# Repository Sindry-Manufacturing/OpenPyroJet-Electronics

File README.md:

# OpenPyroJet-Electronics

Software licensed under: AGPL-3

Hardware licensed under: CERN-OHL-S-V2

These sets of sub-folders contain KiCAD 5.1 based designs for experimenting with a PCB based metal/ceramic 3D Printer. 

Gen3.1_Printhead       ; initial experimental PCB based Printhead

Printhead-Controller   ; HW board that runs the Driver board

Printhead-Driver       ; HW circuitry to drive the printhead

software               ; basic Arduino based software to test the Controller & Driver boards.  See: https://github.com/Sindry-Manufacturing/OpenPyrojet-Jetpack  for a much more complete solution

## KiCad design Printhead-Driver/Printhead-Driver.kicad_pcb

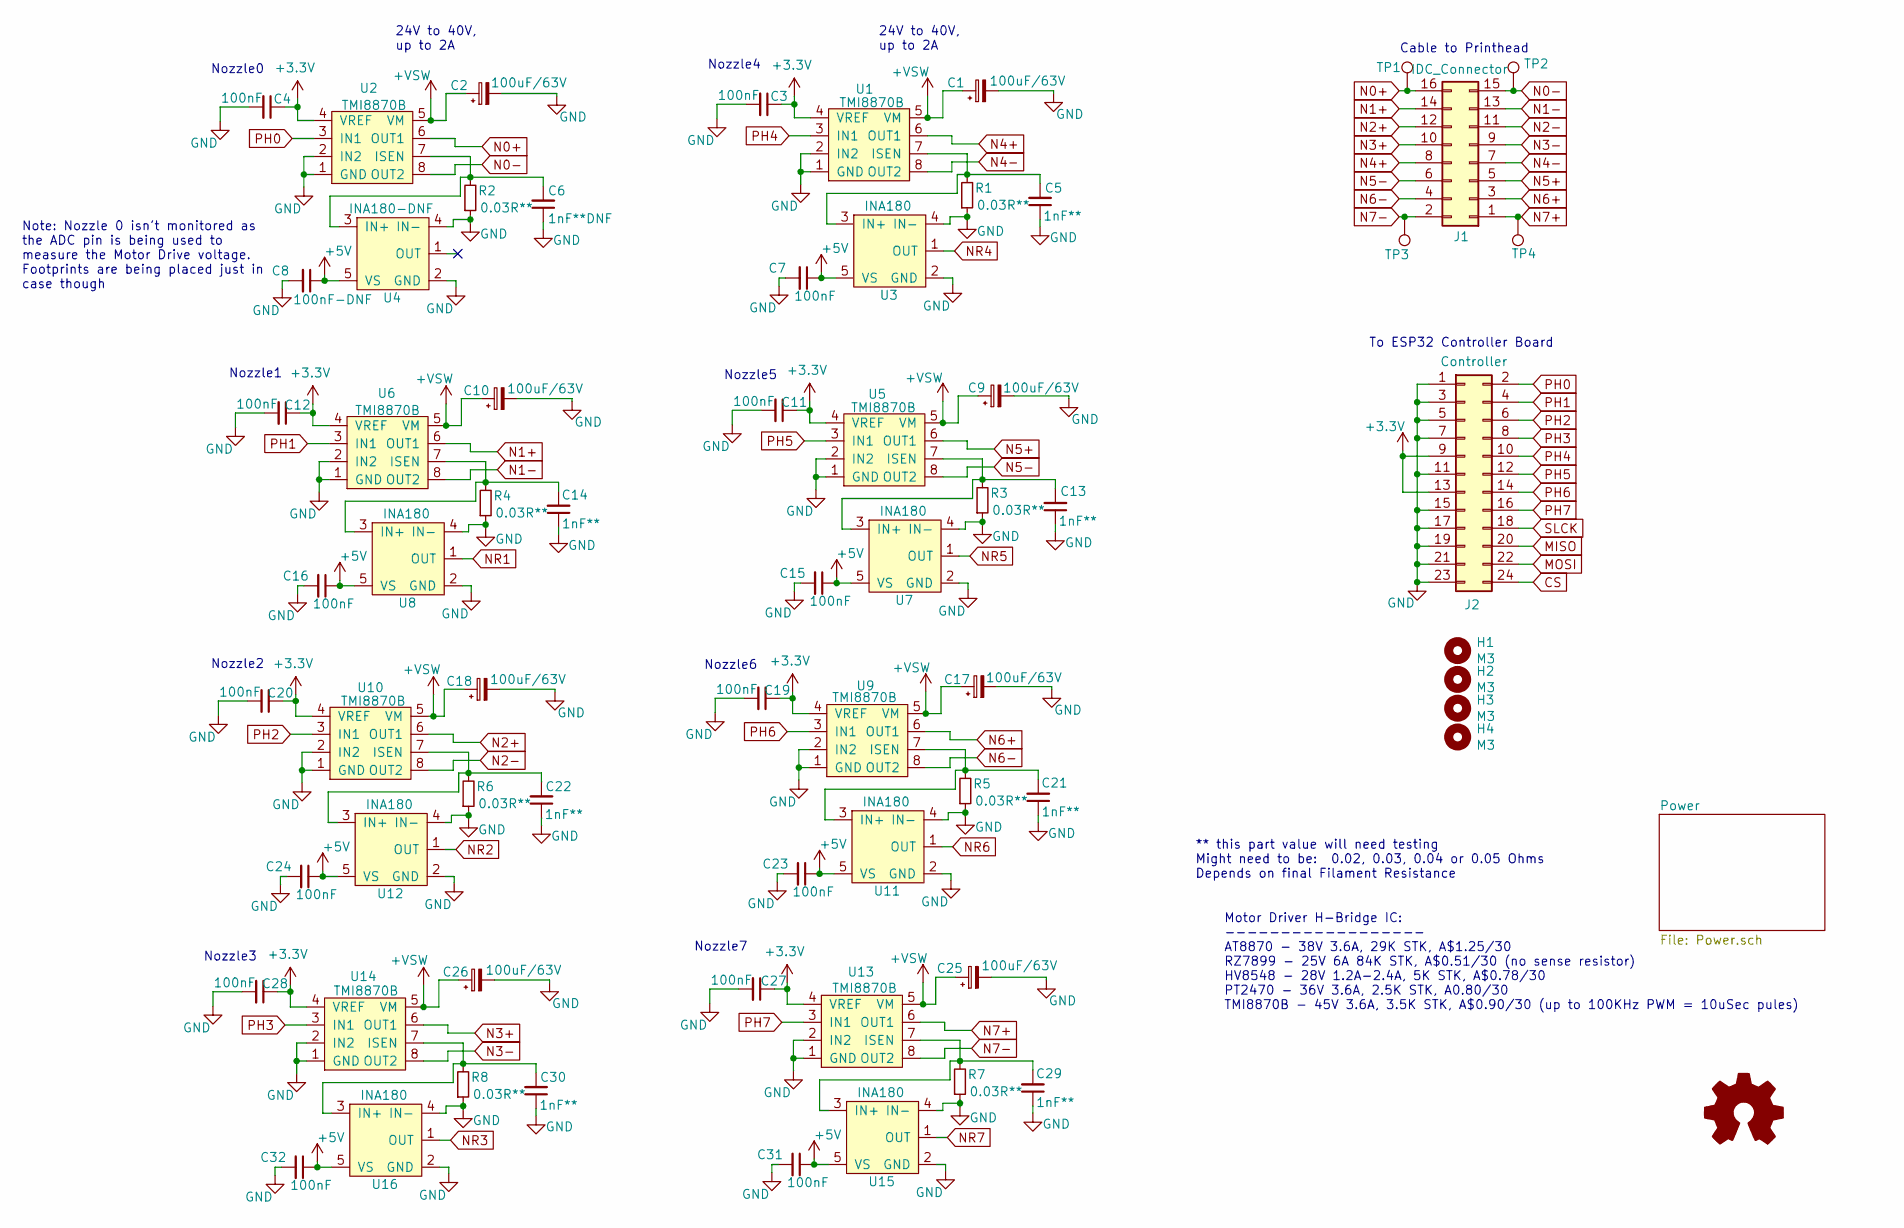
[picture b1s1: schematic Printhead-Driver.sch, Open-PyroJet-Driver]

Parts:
C1, C2, C9, C10, C17, C18, C25, C26: 100uF/63V; CP_Radial_D8.0mm_P3.50mm
C3, C4, C7, C11, C12, C15, C16, C19, C20, C23, C24, C27, C28, C31, C32: 100nF; C_0603_1608Metric
C5, C13, C14, C21, C22, C29, C30: 1nF**; C_0603_1608Metric
C6: 1nF**DNF; C_0603_1608Metric
C8: 100nF-DNF; C_0603_1608Metric
H1, H2, H3, H4: M3; MountingHole_3.2mm_M3
J1: IDC_Connector; IDC-Header_2x08_P2.54mm_Horizontal
J2: Controller; PinHeader_2x12_P2.54mm_Vertical
R1, R2, R3, R4, R5, R6, R7, R8: 0.03R**; R_1206_3216Metric
TP1, TP2, TP3, TP4: TestPoint; TestPoint_THTPad_1.5x1.5mm_Drill0.7mm
U1, U2, U5, U6, U9, U10, U13, U14: TMI8870B; HSOP-8-1EP_3.9x4.9mm_P1.27mm_EP2.41x3.1mm_ThermalVias
U3, U7, U8, U11, U12, U15, U16: INA180; SOT-23-5
U4: INA180-DNF; SOT-23-5

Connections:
+3V3: C3.1, C4.1, C11.1, C12.1, C19.1, C20.1, C27.1, C28.1, J2.9, J2.13, U1.4 (VREF), U2.4 (VREF), U5.4 (VREF), U6.4 (VREF), U9.4 (VREF), U10.4 (VREF), U13.4 (VREF), U14.4 (VREF); also elsewhere on the board
+5V: C7.1, C8.1, C15.1, C16.1, C23.1, C24.1, C31.1, C32.1, U3.5 (VS), U4.5 (VS), U7.5 (VS), U8.5 (VS), U11.5 (VS), U12.5 (VS), U15.5 (VS), U16.5 (VS); also elsewhere on the board
+VSW: C1.1, C2.1, C9.1, C10.1, C17.1, C18.1, C25.1, C26.1, U1.5 (VM), U2.5 (VM), U5.5 (VM), U6.5 (VM), U9.5 (VM), U10.5 (VM), U13.5 (VM), U14.5 (VM); also elsewhere on the board
CS: J2.24; also elsewhere on the board
GND: C1.2, C2.2, C3.2, C4.2, C5.1, C6.1, C7.2, C8.2, C9.2, C10.2, C11.2, C12.2, C13.1, C14.1, C15.2, C16.2, C17.2, C18.2, C19.2, C20.2, C21.1, C22.1, C23.2, C24.2, C25.2, C26.2, C27.2, C28.2, C29.1, C30.1, C31.2, C32.2, J2.1, J2.3, J2.5, J2.7, J2.11, J2.15, J2.17, J2.19, J2.21, J2.23, R1.1, R2.1, R3.1, R4.1, R5.1, R6.1, R7.1, R8.1, U1.1 (GND), U1.2 (IN2), U2.1 (GND), U2.2 (IN2), U3.2 (GND), U3.4 (IN-), U4.2 (GND), U4.4 (IN-), U5.1 (GND), U5.2 (IN2), U6.1 (GND), U6.2 (IN2), U7.2 (GND), U7.4 (IN-), U8.2 (GND), U8.4 (IN-), U9.1 (GND), U9.2 (IN2), U10.1 (GND), U10.2 (IN2), U11.2 (GND), U11.4 (IN-), U12.2 (GND), U12.4 (IN-), U13.1 (GND), U13.2 (IN2), U14.1 (GND), U14.2 (IN2), U15.2 (GND), U15.4 (IN-), U16.2 (GND), U16.4 (IN-); also elsewhere on the board
MISO: J2.20; also elsewhere on the board
MOSI: J2.22; also elsewhere on the board
N0+: J1.16, TP1.1, U2.6 (OUT1)
N0-: J1.15, TP2.1, U2.8 (OUT2)
N1+: J1.14, U6.6 (OUT1)
N1-: J1.13, U6.8 (OUT2)
N2+: J1.12, U10.6 (OUT1)
N2-: J1.11, U10.8 (OUT2)
N3+: J1.10, U14.6 (OUT1)
N3-: J1.9, U14.8 (OUT2)
N4+: J1.8, U1.6 (OUT1)
N4-: J1.7, U1.8 (OUT2)
N5+: J1.5, U5.6 (OUT1)
N5-: J1.6, U5.8 (OUT2)
N6+: J1.3, U9.6 (OUT1)
N6-: J1.4, U9.8 (OUT2)
N7+: J1.1, TP4.1, U13.6 (OUT1)
N7-: J1.2, TP3.1, U13.8 (OUT2)
NR1: U8.1 (OUT); also elsewhere on the board
NR2: U12.1 (OUT); also elsewhere on the board
NR3: U16.1 (OUT); also elsewhere on the board
NR4: U3.1 (OUT); also elsewhere on the board
NR5: U7.1 (OUT); also elsewhere on the board
NR6: U11.1 (OUT); also elsewhere on the board
NR7: U15.1 (OUT); also elsewhere on the board
unnamed: C5.2, R1.2, U1.7 (ISEN), U3.3 (IN+)
unnamed: C6.2, R2.2, U2.7 (ISEN), U4.3 (IN+)
unnamed: C13.2, R3.2, U5.7 (ISEN), U7.3 (IN+)
unnamed: C14.2, R4.2, U6.7 (ISEN), U8.3 (IN+)
unnamed: C21.2, R5.2, U9.7 (ISEN), U11.3 (IN+)
unnamed: C22.2, R6.2, U10.7 (ISEN), U12.3 (IN+)
unnamed: C29.2, R7.2, U13.7 (ISEN), U15.3 (IN+)
unnamed: C30.2, R8.2, U14.7 (ISEN), U16.3 (IN+)
PH0: J2.2, U2.3 (IN1)
PH1: J2.4, U6.3 (IN1)
PH2: J2.6, U10.3 (IN1)
PH3: J2.8, U14.3 (IN1)
PH4: J2.10, U1.3 (IN1)
PH5: J2.12, U5.3 (IN1)
PH6: J2.14, U9.3 (IN1)
PH7: J2.16, U13.3 (IN1)
SLCK: J2.18; also elsewhere on the board

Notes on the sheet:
24V to 40V, up to 2A
Motor Driver H-Bridge IC: ------------------ AT8870 - 38V 3.6A, 29K STK, A$1.25/30 RZ7899 - 25V 6A 84K STK, A$0.51/30 (no sense resistor) HV8548 - 28V 1.2A-2.4A, 5K STK, A$0.78/30 PT2470 - 36V 3.6A, 2.5K STK, A0.80/30 TMI8870B - 45V 3.6A, 3.5K STK, A$0.90/30 (up to 100KHz PWM = 10uSec pules)
** this part value will need testing Might need to be: 0.02, 0.03, 0.04 or 0.05 Ohms Depends on final Filament Resistance
Cable to Printhead
Nozzle0
Nozzle1
Nozzle2
Nozzle3
Nozzle7
Nozzle6
Nozzle5
Nozzle4
To ESP32 Controller Board
Note: Nozzle 0 isn't monitored as the ADC pin is being used to measure the Motor Drive voltage. Footprints are being placed just in case though

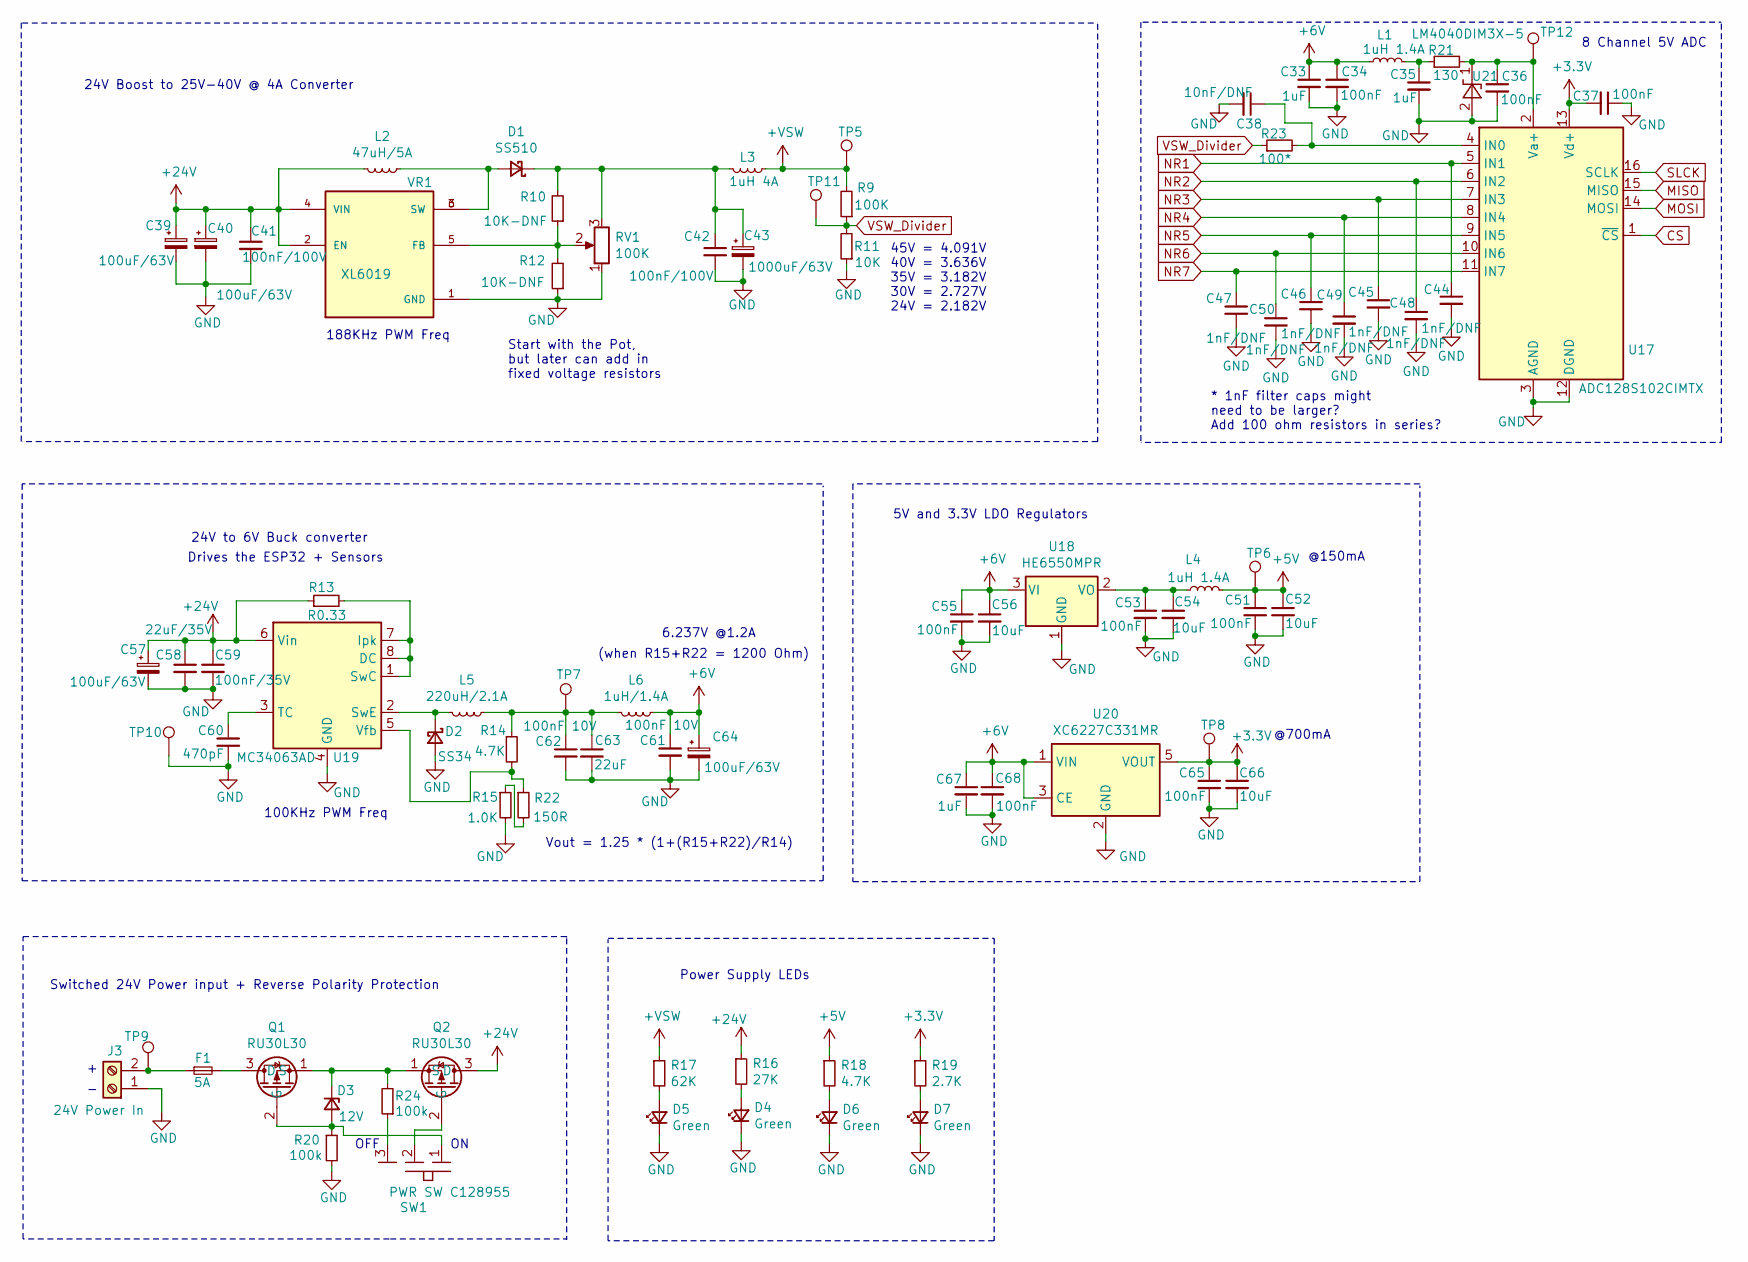
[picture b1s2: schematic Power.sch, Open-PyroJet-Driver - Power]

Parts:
C33, C35, C68: 1uF; C_0603_1608Metric
C34, C36, C37, C51, C53, C55, C65, C67: 100nF; C_0603_1608Metric
C38: 10nF/DNF; C_0603_1608Metric
C39, C40, C57, C64: 100uF/63V; CP_Radial_D8.0mm_P3.50mm
C41, C42: 100nF/100V; C_0603_1608Metric
C43: 1000uF/63V; CP_Radial_D16.0mm_P7.50mm
C44, C45, C46, C47, C48, C49, C50: 1nF/DNF; C_0603_1608Metric
C52, C54, C56, C66: 10uF; C_0603_1608Metric
C58: 22uF/35V; C_1210_3225Metric
C59: 100nF/35V; C_1206_3216Metric
C60: 470pF; C_0603_1608Metric
C61, C62: 100nF 10V; C_0603_1608Metric
C63: 22uF; C_0603_1608Metric
D1: SS510; D_SMA
D2: SS34; D_SMA
D3: 12V; D_SOD-123
D4, D5, D6, D7: Green; D_0603_1608Metric
F1: 5A; Fuse_Holder_1808_10.0mmx5mm
J3: 24V Power In; JST-XH-2P_SMD
L1, L4: 1uH 1.4A; L_0805_2012Metric
L2: 47uH/5A; L_47uH_4A_11mmx10mm_H4.8mm
L3: 1uH 4A; L_Taiyo-Yuden_MD-5050
L5: 220uH/2.1A; L_220uH_2A_15x15mm_H8mm
L6: 1uH/1.4A; L_0805_2012Metric
Q1, Q2: RU30L30; PDFN3333
R9: 100K; R_0603_1608Metric
R10, R12: 10K-DNF; R_0603_1608Metric
R11: 10K; R_0603_1608Metric
R13: R0.33; R_1206_3216Metric
R14, R18: 4.7K; R_0603_1608Metric
R15: 1.0K; R_0603_1608Metric
R16: 27K; R_0603_1608Metric
R17: 62K; R_0603_1608Metric
R19: 2.7K; R_0603_1608Metric
R20, R24: 100k; R_0603_1608Metric
R21: 130; R_0603_1608Metric
R22: 150R; R_0603_1608Metric
R23: 100*; R_0603_1608Metric
RV1: 100K; Potentiometer_Bourns_3266Y_Vertical
SW1: PWR SW C128955; SW_SMD_SPDT_PCM12_7.8x3.8
TP5, TP6, TP7, TP8, TP9, TP10, TP11, TP12: TestPoint; TestPoint_THTPad_1.5x1.5mm_Drill0.7mm
U17: ADC128S102CIMTX; TSSOP-16_4.4x5mm_P0.65mm
U18: HE6550MPR; SOT-89-3
U19: MC34063AD; SOIC-8_3.9x4.9mm_P1.27mm
U20: XC6227C331MR; SOT-23-5
U21: LM4040DIM3X-5; SOT-23
VR1: XL6019; DPAK170P1435X465-6N

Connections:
+3V3: C37.2, C65.1, C66.1, R19.1, TP8.1, U17.13 (Vd+), U20.5 (VOUT); also elsewhere on the board
+5V: C51.1, C52.1, L4.2, R18.1, TP6.1; also elsewhere on the board
+6V: C33.1, C34.1, C55.1, C56.1, C61.1, C64.1, C67.1, C68.1, L1.2, L6.1, U18.3 (VI), U20.1 (VIN), U20.3 (CE)
+24V: C39.1, C40.1, C41.1, C57.1, C58.1, C59.1, L2.2, Q2.3 (D), R13.1, R16.1, U19.6 (Vin), VR1.2 (EN), VR1.4 (VIN)
+VSW: L3.1, R9.2, R17.1, TP5.1; also elsewhere on the board
CS: U17.1 (~CS); also elsewhere on the board
GND: C33.2, C34.2, C35.2, C36.2, C37.1, C38.2, C39.2, C40.2, C41.2, C42.2, C43.2, C44.2, C45.2, C46.2, C47.2, C48.2, C49.2, C50.2, C51.2, C52.2, C53.2, C54.2, C55.2, C56.2, C57.2, C58.2, C59.2, C60.2, C61.2, C62.2, C63.2, C64.2, C65.2, C66.2, C67.2, C68.2, D2.2 (A), D4.1 (K), D5.1 (K), D6.1 (K), D7.1 (K), J3.1, R11.1, R12.1, R15.2, R20.2, RV1.1, TP10.1, U17.3 (AGND), U17.12 (DGND), U18.1 (GND), U19.4 (GND), U20.2 (GND), U21.2 (A), VR1.1 (GND); also elsewhere on the board
MISO: U17.15 (MISO); also elsewhere on the board
MOSI: U17.14 (MOSI); also elsewhere on the board
NR1: C44.1, U17.5 (IN1); also elsewhere on the board
NR2: C48.1, U17.6 (IN2); also elsewhere on the board
NR3: C45.1, U17.7 (IN3); also elsewhere on the board
NR4: C49.1, U17.8 (IN4); also elsewhere on the board
NR5: C46.1, U17.9 (IN5); also elsewhere on the board
NR6: C50.1, U17.10 (IN6); also elsewhere on the board
NR7: C47.1, U17.11 (IN7); also elsewhere on the board
unnamed: C35.1, L1.1, R21.1
unnamed: C36.1, R21.2, TP12.1, U17.2 (Va+), U21.1 (K)
unnamed: C38.1, R23.2, U17.4 (IN0)
unnamed: C42.1, C43.1, D1.1 (K), L3.2, R10.2, RV1.3
unnamed: C53.1, C54.1, L4.1, U18.2 (VO)
unnamed: C60.1, U19.3 (TC)
unnamed: C62.1, C63.1, L5.1, L6.2, R14.1, TP7.1
unnamed: D1.2 (A), L2.1, VR1.3 (SW), VR1.6 (SW)
unnamed: D2.1 (K), L5.2, U19.2 (SwE)
unnamed: D3.1 (K), Q1.1 (S), Q2.1 (S), R24.2
unnamed: D3.2 (A), Q1.2 (G), R20.1, SW1.1
unnamed: D4.2 (A), R16.2
unnamed: D5.2 (A), R17.2
unnamed: D6.2 (A), R18.2
unnamed: D7.2 (A), R19.2
unnamed: F1.1, J3.2, TP9.1
unnamed: F1.2, Q1.3 (D)
unnamed: Q2.2 (G), SW1.2
unnamed: R10.1, R12.2, RV1.2, VR1.5 (FB)
unnamed: R13.2, U19.1 (SwC), U19.7 (Ipk), U19.8 (DC)
unnamed: R14.2, R22.1, U19.5 (Vfb)
unnamed: R15.1, R22.2
unnamed: R24.1, SW1.3
SLCK: U17.16 (SCLK); also elsewhere on the board
VSW_Divider: R9.1, R11.2, R23.1, TP11.1

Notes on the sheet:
24V to 6V Buck converter
Drives the ESP32 + Sensors
Start with the Pot, but later can add in fixed voltage resistors
Power Supply LEDs
Switched 24V Power input + Reverse Polarity Protection
@700mA
45V = 4.091V 40V = 3.636V 35V = 3.182V 30V = 2.727V 24V = 2.182V
@150mA
5V and 3.3V LDO Regulators
8 Channel 5V ADC
24V Boost to 25V-40V @ 4A Converter
188KHz PWM Freq
100KHz PWM Freq
* 1nF filter caps might need to be larger? Add 100 ohm resistors in series?
6.237V @1.2A
(when R15+R22 = 1200 Ohm)
Vout = 1.25 * (1+(R15+R22)/R14)
OFF

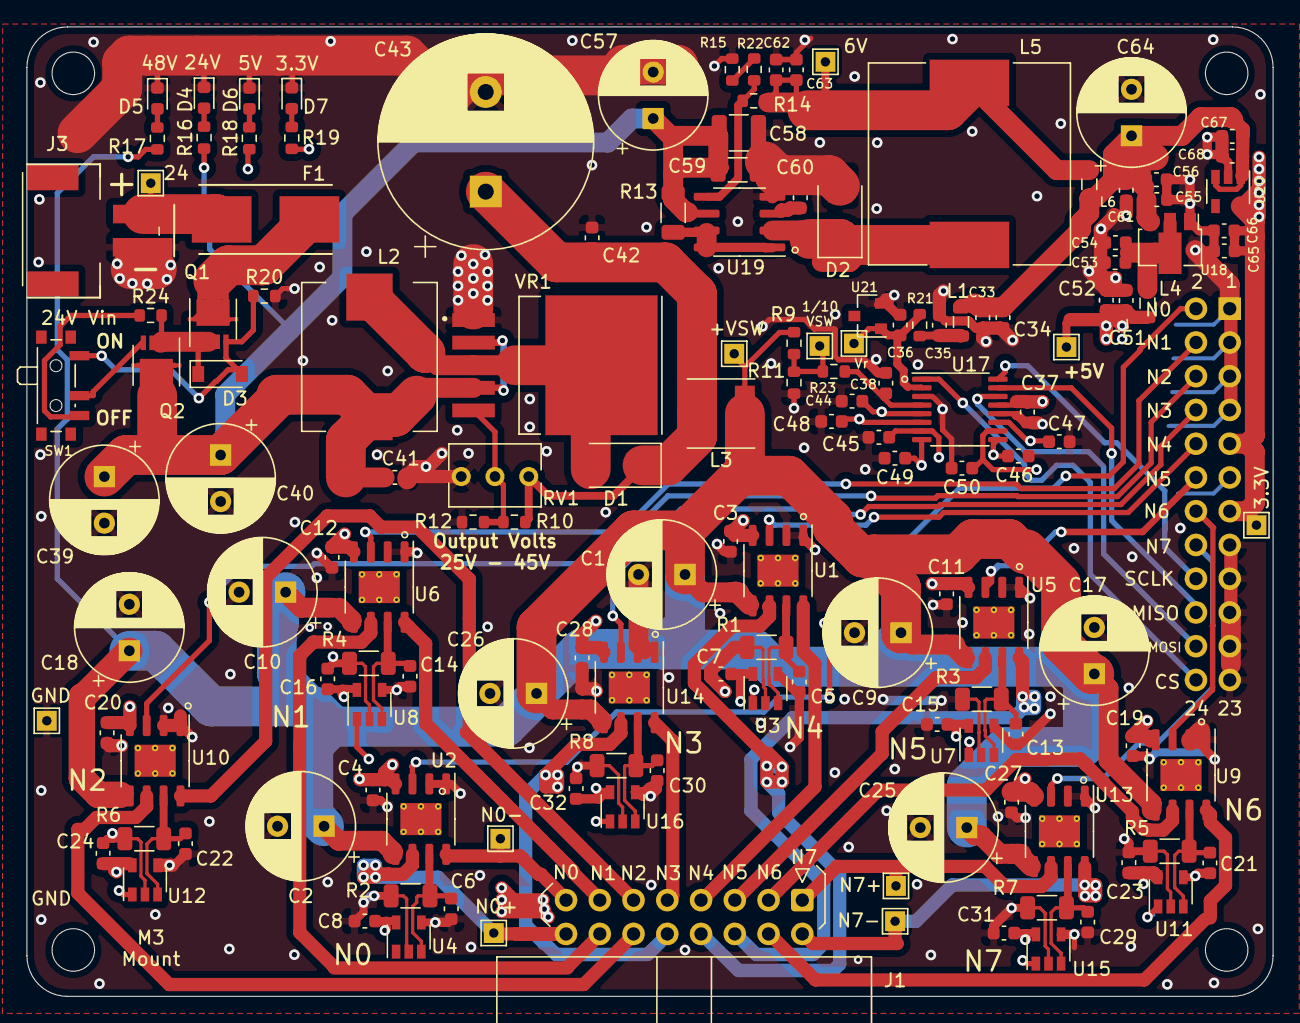
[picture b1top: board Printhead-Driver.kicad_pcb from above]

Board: 4 copper layers, 93.8 x 73.0 mm, 151 parts (1 on the bottom side), 73 nets.

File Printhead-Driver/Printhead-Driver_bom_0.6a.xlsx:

References | Value | Footprint | Quantity Per PCB | Location | LCSC P/N
C60 | 470pF | C_0603_1608Metric | 1 | 92-2 | C107092
C3 C4 C7 C11 C12 C15 C16 C19 C20 C23 C24 C27 C28 C31 C32 C34 C36 C37 C51 C53 C5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 | 100nF | C_0603_1608Metric | 23 | T15 | C108079 | 6.3V or higher
C33 C35 C68 | 1uF | C_0603_1608Metric | 3 | T15 | C69335
C52 C54 C56 C66 | 10uF | C_0603_1608Metric | 4 | T15 | C326057
C63 | 22uF | C_0603_1608Metric | 1 | T15 | C59461
C43 | 1000uF/63V | CP_Radial_D16.0mm_P7.50mm | 1 | 96-28 | C10744
C61 C62 | 100nF 10V | C_0603_1608Metric | 2 | T15 | C108079
C8 | 100nF-DNF | C_0603_1608Metric | 1 | T15 | C108079
C41 C42 | 100nF/100V | C_0603_1608Metric | 2 | 92-2 | C113803
C59 | 100nF/35V | C_1206_3216Metric | 1 | 92-2 | C113803
C1 C2 C9 C10 C17 C18 C25 C26 C39 C40 C57 C64 | 100uF/63V | CP_Radial_D8.0mm_P3.50mm | 12 | 96-20 | C365794
C5 C13 C14 C21 C22 C29 C30 | 1nF** | C_0603_1608Metric | 7 |  | C100040 | Just a guestimate. Final value needs testing
C6 | 1nF**DNF | C_0603_1608Metric | 1 |  | C100040 | Just a guestimate. Final value needs testing
C38 C44 C45 C46 C47 C48 C49 C50 | 1nF/DNF | C_0603_1608Metric | 8 |  | C100040 | Just a guestimate. Final value needs testing
C58 | 22uF/35V | C_1210_3225Metric | 1 |  | C2891987
D3 | 12V-Zener_Diode | D_0805_2012Metric | 1 |  | C21567
D4 D5 D6 D7 | Green | D_0603_1608Metric | 4 | T15 | C142303
D2 | SS34 | D_SMA | 1 | T6 | C8678
D1 | SS510 | D_SMA | 1 | 91-31 | C65010
F1 | 5A | Fuse_Holder_1808_10.0mmx5mm | 1 | Fuse Tray | C206917
J3 | 24V Power In | JST-XH-2P_SMD | 1 | tray | C64520
J2 - hand solder | Controller | PinHeader_2x12_P2.54mm_Vertical | 1 |  |  | can use normal Pinheader parts
J1 - hand solder | IDC_Connector | IDC-Header_2x08_P2.54mm_Horizontal | 1 |  |  | can use normal Pinheader parts
L1 L4 | 1uH 1.4A | L_0805_2012Metric | 2 |  | C281114
L3 | 1uH 4A | L_1uH 4A or more | 1 |  | C2929426
L6 | 1uH/1.4A | L_0805_2012Metric | 1 |  | C281114
L5 | 220uH/2.1A | L_220uH_2A_15x15mm_H8mm | 1 | 96-11 | C970547
L2 | 47uH/5A | L_47uH_4A_11mmx10mm_H4.8mm | 1 | 96-13 | C2847567
Q1 | RU30L30 | PDFN3333 | 1 | 88-22 | C128588
R15 | 1.3K | R_0603_1608Metric | 1 | Book | C22767
R19 | 2.7K | R_0603_1608Metric | 1 | T1 | C13167
R14 R18 | 4.7K | R_0603_1608Metric | 2 | T1 | C23162
R11 | 10K (12K) | R_0603_1608Metric | 1 | T1 | C25804 | Use 10K instead of 12K
R16 | 27K | R_0603_1608Metric | 1 | Book | C22967
R17 | 62K | R_0603_1608Metric | 1 | Book | C23221
R9 | 100K (88K) | R_0603_1608Metric | 1 | T1 | C25803 | Use 100K instead of 88K
R20 | 100k | R_0603_1608Metric | 1 | T1 | C25803
R1 R2 R3 R4 R5 R6 R7 R8 | 0.03R** | R_1206_3216Metric | 8 | T17 | C2903497 | might need to be: .02, .03, .04 or .05 ohms? Depends on PH nozzle resistance
R10 R12 | 10K-DNF | R_0603_1608Metric | 2 | T1 | C25804
R13 | R0.33 | R_1206_3216Metric | 1 | T17 | C2932844
RV1 | 100K | Potentiometer_Bourns_3266Y_Vertical | 1 | 96-21 | C118963
U17 | ADC128S102CIMTX | TSSOP-16_4.4x5mm_P0.65mm | 1 |  | C179666
U18 | HE6550MPR | SOT-89-3 | 1 |  | C711959
U3 U7 U8 U11 U12 U15 U16 | INA180A2IDBVR | SOT-23-5 | 7 |  | C192764
U4 | INA180A2IDBVR-DNF | SOT-23-5 | 1 |  | C192764
U19 | MC34063AD | SOIC-8_3.9x4.9mm_P1.27mm | 1 | 96-11 | C32078
U1 U2 U5 U6 U9 U10 U13 U14 | TMI8870B | HSOP-8-1EP_3.9x4.9mm_P1.27mm_EP2.41x3.1mm_ThermalVias | 8 | 96-15 | C2889167
U20 | XC6227C331MR | SOT-23-5 | 1 |  | C216640
VR1 | XL6019 | DPAK170P1435X465-6N | 1 | 88-38/ 96-13 | C73018
Component Groups: | 49
Total components: | 128
Schematic Version: | 0.6a
Schematic Date: | 44692
BoM Date: | 44692.736377314817
Schematic Source: | Printhead-Driver.sch

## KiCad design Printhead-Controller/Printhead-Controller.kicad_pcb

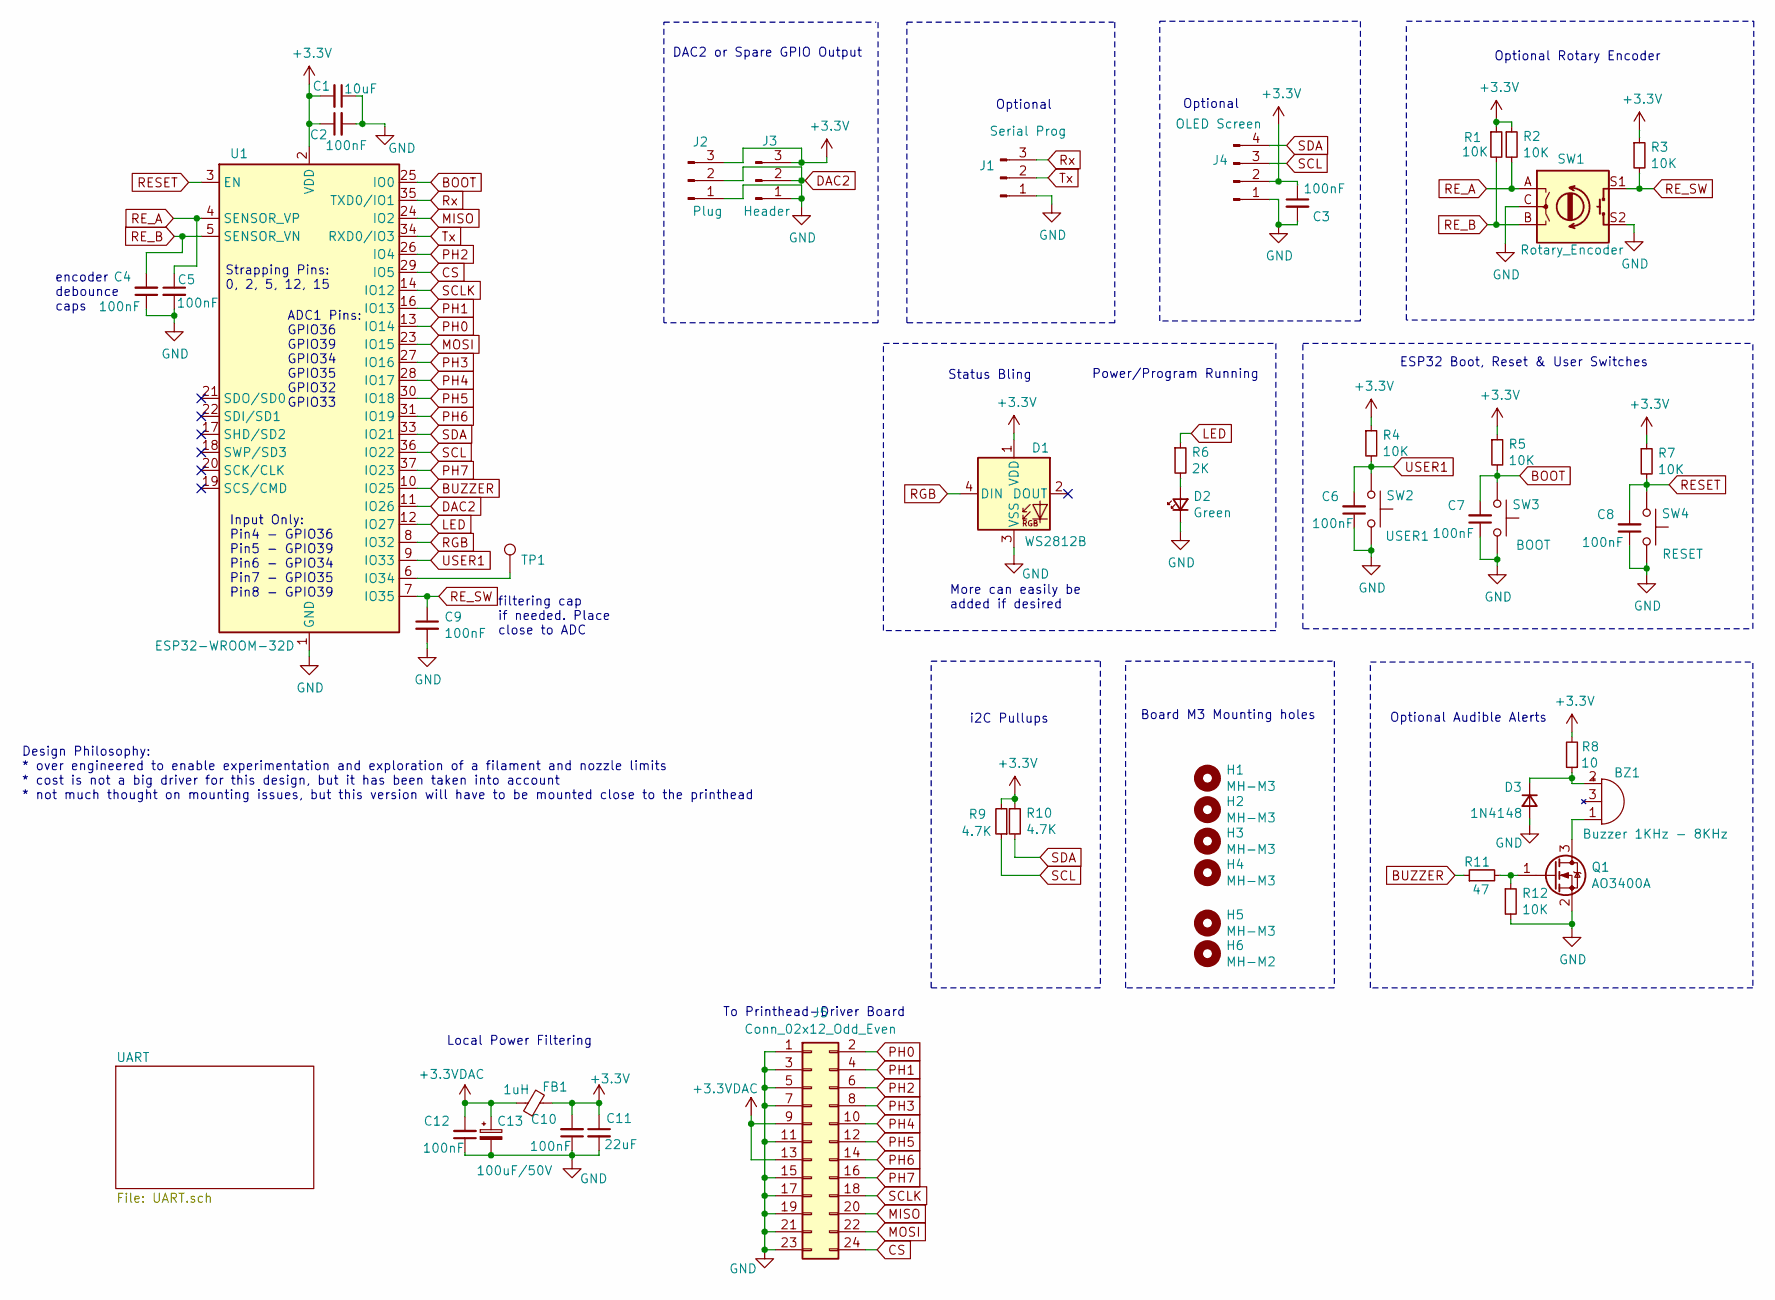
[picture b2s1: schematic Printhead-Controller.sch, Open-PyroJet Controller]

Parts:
BZ1: Buzzer 1KHz - 8KHz; MagneticBuzzer_5.2x5.2_4KHz
C1: 10uF; C_0603_1608Metric
C2, C3, C4, C5, C6, C7, C8, C9, C10, C12: 100nF; C_0603_1608Metric
C11: 22uF; C_0603_1608Metric
C13: 100uF/50V; CP_Radial_D8.0mm_P3.50mm
D1: WS2812B; LED_WS2812B_PLCC4_5.0x5.0mm_P3.2mm
D2: Green; LED_0603_1608Metric
D3: 1N4148; D_0805_2012Metric
FB1: 1uH; R_0805_2012Metric
H1, H2, H3, H4, H5: MH-M3; MountingHole_3.2mm_M3
H6: MH-M2; MountingHole_2.2mm_M2
J1: Serial Prog; PinHeader_1x03_P1.27mm_Vertical
J2: Plug; Hirose_DF13C_CL535-0403-5-51_1x03-1MP_P1.25mm_Vertical
J3: Header; PinHeader_1x03_P2.54mm_Vertical
J4: OLED Screen; PinHeader_1x04_P2.54mm_Vertical
J5: Conn_02x12_Odd_Even; PinHeader_2x12_P2.54mm_Vertical
Q1: AO3400A; SOT-23
R1, R2, R3, R4, R5, R7, R12: 10K; R_0603_1608Metric
R6: 2K; R_0603_1608Metric
R8: 10; R_0805_2012Metric
R9, R10: 4.7K; R_0603_1608Metric
R11: 47; R_0603_1608Metric
SW1: Rotary_Encoder; RotaryEncoder_Alps_EC11E-Switch_Vertical_H20mm
SW2: USER1; SW_SMD_SPST_SKQG_WithStem_6x6.5
SW3: BOOT; SMD_Switch_5x3
SW4: RESET; SMD_Switch_5x3
TP1: TestPoint; TestPoint_THTPad_1.5x1.5mm_Drill0.7mm
U1: ESP32-WROOM-32D; ESP32-WROOM-32

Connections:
+3.3VDAC: C12.2, C13.1, FB1.1, J5.9, J5.13
BOOT: C7.2, R5.2, SW3.1, U1.25 (IO0); also elsewhere on the board
BUZZER: R11.1, U1.10 (IO25)
CS: J5.24, U1.29 (IO5)
DAC2: J2.2, J3.2, U1.11 (IO26)
GND: C1.1, C2.2, C3.2, C4.1, C5.2, C6.1, C7.1, C8.1, C9.2, C10.1, C11.2, C12.1, C13.2, D1.3 (VSS), D2.1 (K), D3.2 (A), J1.1, J2.1, J3.1, J4.1, J5.1, J5.3, J5.5, J5.7, J5.11, J5.15, J5.17, J5.19, J5.21, J5.23, Q1.2 (S), R12.2, SW1.C, SW1.S2, SW2.2, SW3.2, SW4.2, U1.1 (GND), U1.15 (GND), U1.38 (GND), U1.39 (GND); also elsewhere on the board
LED: R6.1, U1.12 (IO27)
MISO: J5.20, U1.24 (IO2)
MOSI: J5.22, U1.23 (IO15)
unnamed: BZ1.1 (-), Q1.3 (D)
unnamed: BZ1.2 (+), D3.1 (K), R8.1
unnamed: D2.2 (A), R6.2
unnamed: Q1.1 (G), R11.2, R12.1
unnamed: TP1.1, U1.6 (IO34)
PH0: J5.2, U1.13 (IO14)
PH1: J5.4, U1.16 (IO13)
PH2: J5.6, U1.26 (IO4)
PH3: J5.8, U1.27 (IO16)
PH4: J5.10, U1.28 (IO17)
PH5: J5.12, U1.30 (IO18)
PH6: J5.14, U1.31 (IO19)
PH7: J5.16, U1.37 (IO23)
RESET: C8.2, R7.2, SW4.1, U1.3 (EN); also elsewhere on the board
RE_A: C5.1, R2.2, SW1.A, U1.4 (SENSOR_VP)
RE_B: C4.2, R1.2, SW1.B, U1.5 (SENSOR_VN)
RE_SW: C9.1, R3.2, SW1.S1, U1.7 (IO35)
RGB: D1.4 (DIN), U1.8 (IO32)
Rx: J1.3, U1.35 (TXD0/IO1); also elsewhere on the board
SCL: J4.3, R9.1, U1.36 (IO22)
SCLK: J5.18, U1.14 (IO12)
SDA: J4.4, R10.2, U1.33 (IO21)
Tx: J1.2, U1.34 (RXD0/IO3); also elsewhere on the board
USER1: C6.2, R4.2, SW2.1, U1.9 (IO33)

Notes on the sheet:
Input Only: Pin4 - GPIO36 Pin5 - GPIO39 Pin6 - GPIO34 Pin7 - GPIO35 Pin8 - GPIO39
Strapping Pins: 0, 2, 5, 12, 15
ADC1 Pins: GPIO36 GPIO39 GPIO34 GPIO35 GPIO32 GPIO33
Optional
Optional Rotary Encoder
ESP32 Boot, Reset & User Switches
Power/Program Running
Status Bling
More can easily be added if desired
Design Philosophy: * over engineered to enable experimentation and exploration of a filament and nozzle limits * cost is not a big driver for this design, but it has been taken into account * not much thought on mounting issues, but this version will have to be mounted close to the printhead
Optional Audible Alerts
encoder debounce caps
Board M3 Mounting holes
filtering cap if needed. Place close to ADC
To Printhead-Driver Board
i2C Pullups
Local Power Filtering
DAC2 or Spare GPIO Output

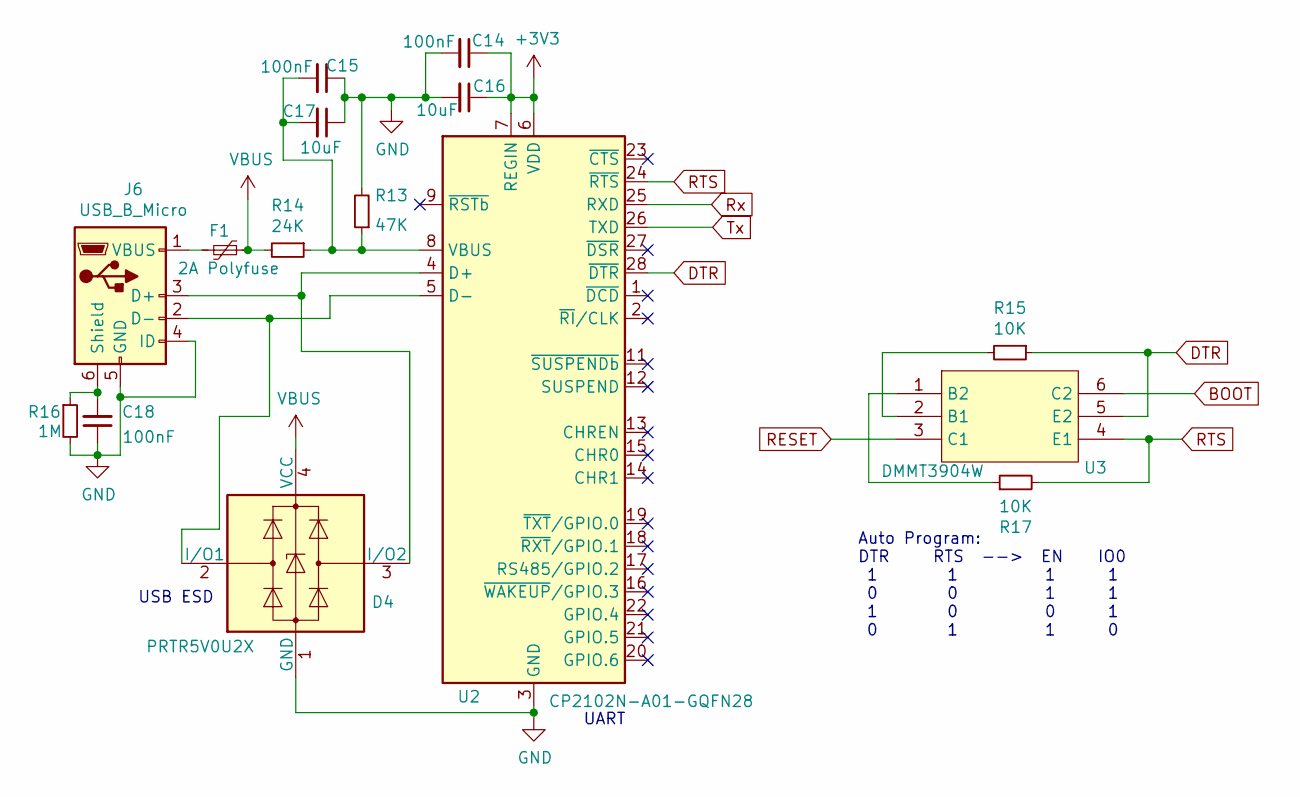
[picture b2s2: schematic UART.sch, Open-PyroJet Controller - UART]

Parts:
C14, C15, C18: 100nF; C_0603_1608Metric
C16, C17: 10uF; C_0603_1608Metric
D4: PRTR5V0U2X; SOT-143
F1: 2A Polyfuse; C_0805_2012Metric
J6: USB_B_Micro; USB_Micro-B_C319160
R13: 47K; R_0603_1608Metric
R14: 24K; R_0603_1608Metric
R15, R17: 10K; R_0603_1608Metric
R16: 1M; R_0603_1608Metric
U2: CP2102N-A01-GQFN28; QFN-28-1EP_5x5mm_P0.5mm_EP3.35x3.35mm
U3: DMMT3904W; SOT-363_SC-70-6

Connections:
BOOT: U3.6 (C2); also elsewhere on the board
DTR: R15.1, U2.28 (~DTR), U3.5 (E2)
GND: C14.2, C15.1, C16.2, C17.1, C18.1, D4.1 (GND), J6.4 (ID), J6.5 (GND), R13.2, R16.2, U2.3 (GND), U2.29 (GND); also elsewhere on the board
unnamed: C15.2, C17.2, R13.1, R14.1, U2.8 (VBUS)
unnamed: C18.2, J6.6 (Shield), R16.1
unnamed: D4.2 (I/O1), J6.2 (D-), U2.5 (D-)
unnamed: D4.3 (I/O2), J6.3 (D+), U2.4 (D+)
unnamed: F1.2, J6.1 (VBUS)
unnamed: R15.2, U3.2 (B1)
unnamed: R17.1, U3.1 (B2)
RESET: U3.3 (C1); also elsewhere on the board
RTS: R17.2, U2.24 (~RTS), U3.4 (E1)
Rx: U2.25 (RXD); also elsewhere on the board
Tx: U2.26 (TXD); also elsewhere on the board
VBUS: D4.4 (VCC), F1.1, R14.2

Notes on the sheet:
Auto Program: DTR RTS --> EN IO0 1 1 1 1 0 0 1 1 1 0 0 1 0 1 1 0
USB ESD
UART

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
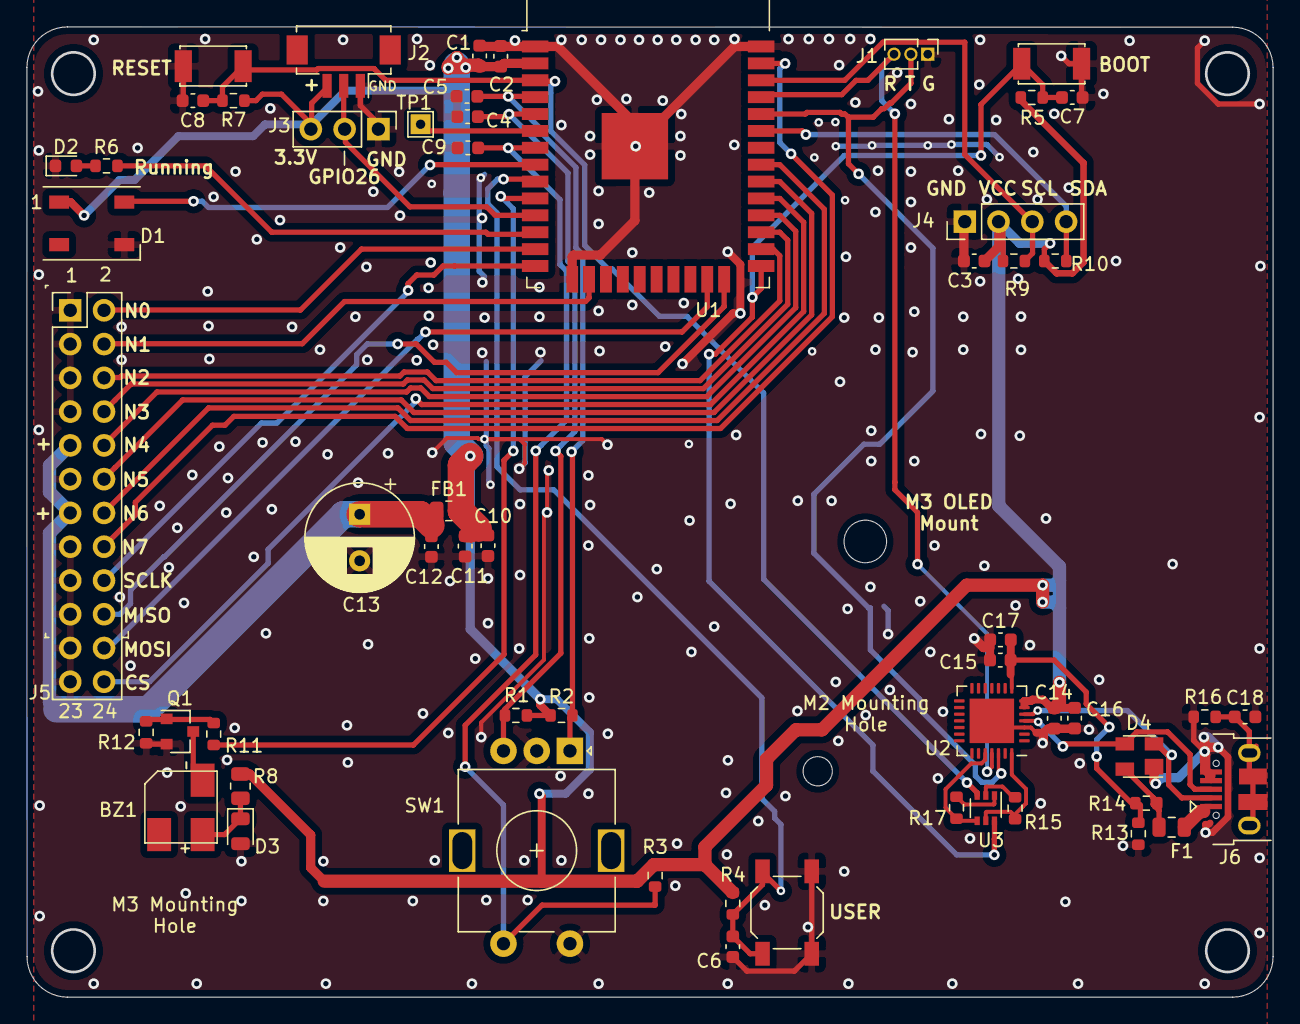
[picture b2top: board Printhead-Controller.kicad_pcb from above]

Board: 2 copper layers, 93.7 x 73.0 mm, 63 parts (0 on the bottom side), 44 nets.

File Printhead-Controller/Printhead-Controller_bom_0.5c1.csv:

References,Value,Footprint,Quantity Per PCB,Location
BZ1,Buzzer 1KHz - 8KHz,MagneticBuzzer_5.2x5.2_4KHz,1,93-6
C2 C3 C5 C6 C7 C8 C9 C10 C12 C14 C15 C18,100nF,C_0603_1608Metric,12,T15
C1 C4 C16 C17,10uF,C_0603_1608Metric,4,T15
C11,22uF,C_0603_1608Metric,1,T15
C13,100uF/50V,CP_Radial_D8.0mm_P3.50mm,1,
D3,1N4148,D_0805_2012Metric,1,T9
D2,Green,LED_0603_1608Metric,1,T15
D4,PRTR5V0U2X,SOT-143,1,
D1,WS2812B,LED_WS2812B_PLCC4_5.0x5.0mm_P3.2mm,1,86-38
F1,2A Polyfuse,C_0805_2012Metric,1,T8
FB1,1uH,R_0805_2012Metric,1,T15
J4,USB_B_Micro,USB_Micro-B_C319160,1,Table
JP1 JP2,Jumper_NC_Small,R_0402_1005Metric,2,87-2?
Q1,AO3400A,SOT-23,1,T9
R8,10,R_0805_2012Metric,1,T2?
R11,47,R_0603_1608Metric,1,T1
R6,2K,R_0603_1608Metric,1,T1
R9 R10,4.7K,R_0603_1608Metric,2,T1
R1 R2 R3 R4 R5 R7 R12,10K,R_0603_1608Metric,7,T1
R15 R17,12K,R_0402_1005Metric,2,87-2
R14,24K,R_0402_1005Metric,1,87-2
R13,47K,R_0402_1005Metric,1,87-2
R16,1M,R_0603_1608Metric,1,T1
SW3,BOOT,SMD_Switch_5x3,1,table
SW4,RESET,SMD_Switch_5x3,1,Table
SW1,Rotary_Encoder,RotaryEncoder_Alps_EC11E-Switch_Vertical_H20mm,1,93-10
SW2,USER1,SW_SMD_SPST_SKQG_WithStem_6x6.5,1,table
U2,CP2102N-A01-GQFN28,QFN-28-1EP_5x5mm_P0.5mm_EP3.35x3.35mm,1,T12/86-4
U3,DMMT3904W,SOT-363_SC-70-6,1,T7
U1,ESP32-WROOM-32D,ESP32-WROOM-32,1,88-70
,,,,
Component Groups:,33,,,
Component Count:,56,,,
Schematic Version:,0.5c1,,,
Schematic Date:,16/03/2022,,,
BoM Date:,18/03/2022 13:29,,,
Schematic Source:,Printhead-Controller.sch,,,
